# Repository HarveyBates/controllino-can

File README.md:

# Controllino-CAN
Small PCB that fits onto the header of a [Controllino-MEGA](https://www.controllino.com/product/controllino-mega/) allowing it to interface with CAN devices through SPI. Does not take up any output/input pins!

## Example Code
Utilises the [MCP2515 arduino library](https://github.com/autowp/arduino-mcp2515). See futher information in the [examples folder](https://github.com/HarveyBates/controllino-can/tree/main/examples).

```cpp
#include <Controllino.h>
#include "mcp2515.h"

#define BIT_RATE CAN_500KBPS
#define NODE_ID 0x0A // Node-ID = 10
#define FUNCTION_CODE 0x180 // CANopen PDO1_TX

// Setup MCP2515 lib with SPI chip-select pin
MCP2515 can(CONTROLLINO_PIN_HEADER_SS);

void setup() {
  Serial.begin(115200);
  Controllino_RTC_init();
  can.reset();
  can.setBitrate(BIT_RATE, MCP_8MHZ);
  can.setNormalMode();
}

void loop() {
  can_frame frame{};
  frame.can_dlc = 8;
  frame.can_id = FUNCTION_CODE | NODE_ID;
  if (can.sendMessage(&frame) == MCP2515::ERROR_OK) {
    Serial.println("TX");
  } else {
    Serial.println("ERR");
  }
  delay(5000);
}
```

## BOM
The bill-of-materials can be found [here](https://github.com/HarveyBates/controllino-can/blob/main/bom/controllino-can-digikey.csv). **The componets only cost $12 AUD ($8 USD).**

## PCB ordering
Compress the [gerber folder](https://github.com/HarveyBates/controllino-can/tree/main/electronics/gerber) and upload to your PCB manufactuer of choice (e.g. [jlcpcb]([https://jlcpcb.com/](https://cart.jlcpcb.com/quote/)https://cart.jlcpcb.com/quote/) or [PCBway](https://www.pcbway.com/) etc.). As the components are SMD (0805 smallest size) get a stencil (top-side of PCB only) to make assembly easier. **PCB plus stencil is roughly $15 AUD ($10 USD).**

## Licence
Controllino-CAN is licenced under the GNU General Public Licence v3.0 as outlined in the [LICENCE](https://github.com/HarveyBates/controllino-can/blob/main/LICENSE).

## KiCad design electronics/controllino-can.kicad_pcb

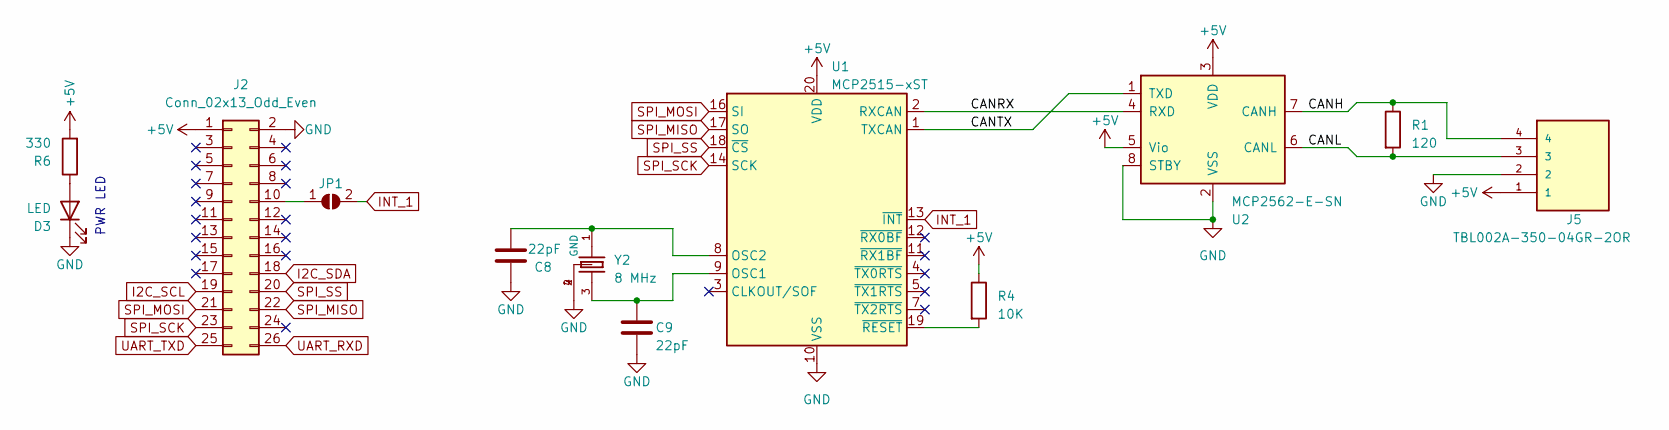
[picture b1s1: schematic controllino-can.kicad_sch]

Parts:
C8, C9: 22pF; C_0805_2012Metric_Pad1.18x1.45mm_HandSolder
D3: LED; LED_0805_2012Metric
J2: Conn_02x13_Odd_Even; PinSocket_2x13_P2.54mm_Vertical
J5: TBL002A-350-04GR-2OR; PARTREV 1.0
JP1: SolderJumper_2_Open; SolderJumper-2_P1.3mm_Open_Pad1.0x1.5mm
R1: 120; R_0805_2012Metric_Pad1.20x1.40mm_HandSolder
R4: 10K; R_0805_2012Metric_Pad1.20x1.40mm_HandSolder
R6: 330; R_0805_2012Metric_Pad1.20x1.40mm_HandSolder
U1: MCP2515-xST; TSSOP-20_4.4x6.5mm_P0.65mm
U2: MCP2562-E-SN; SOIC-8_3.9x4.9mm_P1.27mm
Y2: 8 MHz; ECS-80-12-33-JGN-TR

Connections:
+5V: J2.1, J5.1, R4.1, R6.2, U1.20 (VDD), U2.3 (VDD), U2.5 (Vio)
/CANH: J5.4, R1.1, U2.7 (CANH)
/CANL: J5.3, R1.2, U2.6 (CANL)
/CANRX: U1.2 (RXCAN), U2.4 (RXD)
/CANTX: U1.1 (TXCAN), U2.1 (TXD)
GND: C8.1, C9.2, D3.1 (K), J2.2, J5.2, U1.10 (VSS), U2.2 (VSS), U2.8 (STBY), Y2.2 (GND), Y2.4
I2C_SCL: J2.19
I2C_SDA: J2.18
INT_1: JP1.2 (B), U1.13 (~INT)
unnamed: D3.2 (A), R6.1
unnamed: J2.10, JP1.1 (A)
unnamed: C9.1, U1.9 (OSC1), Y2.3
unnamed: C8.2, U1.8 (OSC2), Y2.1
unnamed: R4.2, U1.19 (~RESET)
SPI_MISO: J2.22, U1.17 (SO)
SPI_MOSI: J2.21, U1.16 (SI)
SPI_SCK: J2.23, U1.14 (SCK)
SPI_SS: J2.20, U1.18 (~CS)
UART_RXD: J2.26
UART_TXD: J2.25

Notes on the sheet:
PWR LED

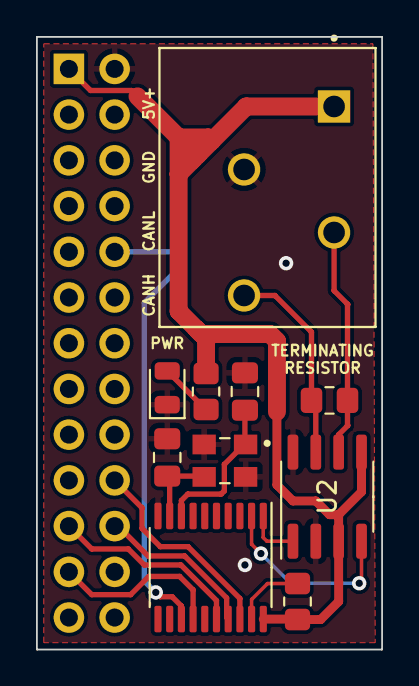
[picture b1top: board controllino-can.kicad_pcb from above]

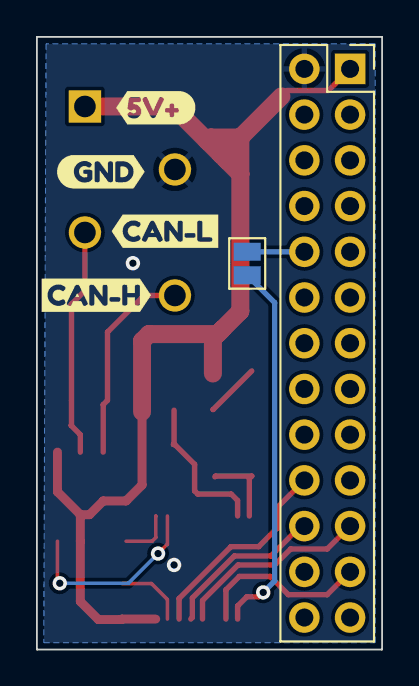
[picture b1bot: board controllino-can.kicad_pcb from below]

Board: 2 copper layers, 19.2 x 34.0 mm, 16 parts (6 on the bottom side), 16 nets.

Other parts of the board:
kibuzzard-653F042B: G***; kibuzzard-653F042B
kibuzzard-653F047F: G***; kibuzzard-653F047F
kibuzzard-653F0443: G***; kibuzzard-653F0443
kibuzzard-653F0498: G***; kibuzzard-653F0498

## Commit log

2023-10-30 added an example
2023-10-30 removed backups
2023-10-30 updated pcb silkscreen and added pcb render. Also added BOM for digikey
2023-10-30 Create LICENSE
2023-10-30 added schematic
